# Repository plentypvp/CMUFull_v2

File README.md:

# CMUFull_v2
Цветомузыка на nRF52840. Фото и видео скоро!

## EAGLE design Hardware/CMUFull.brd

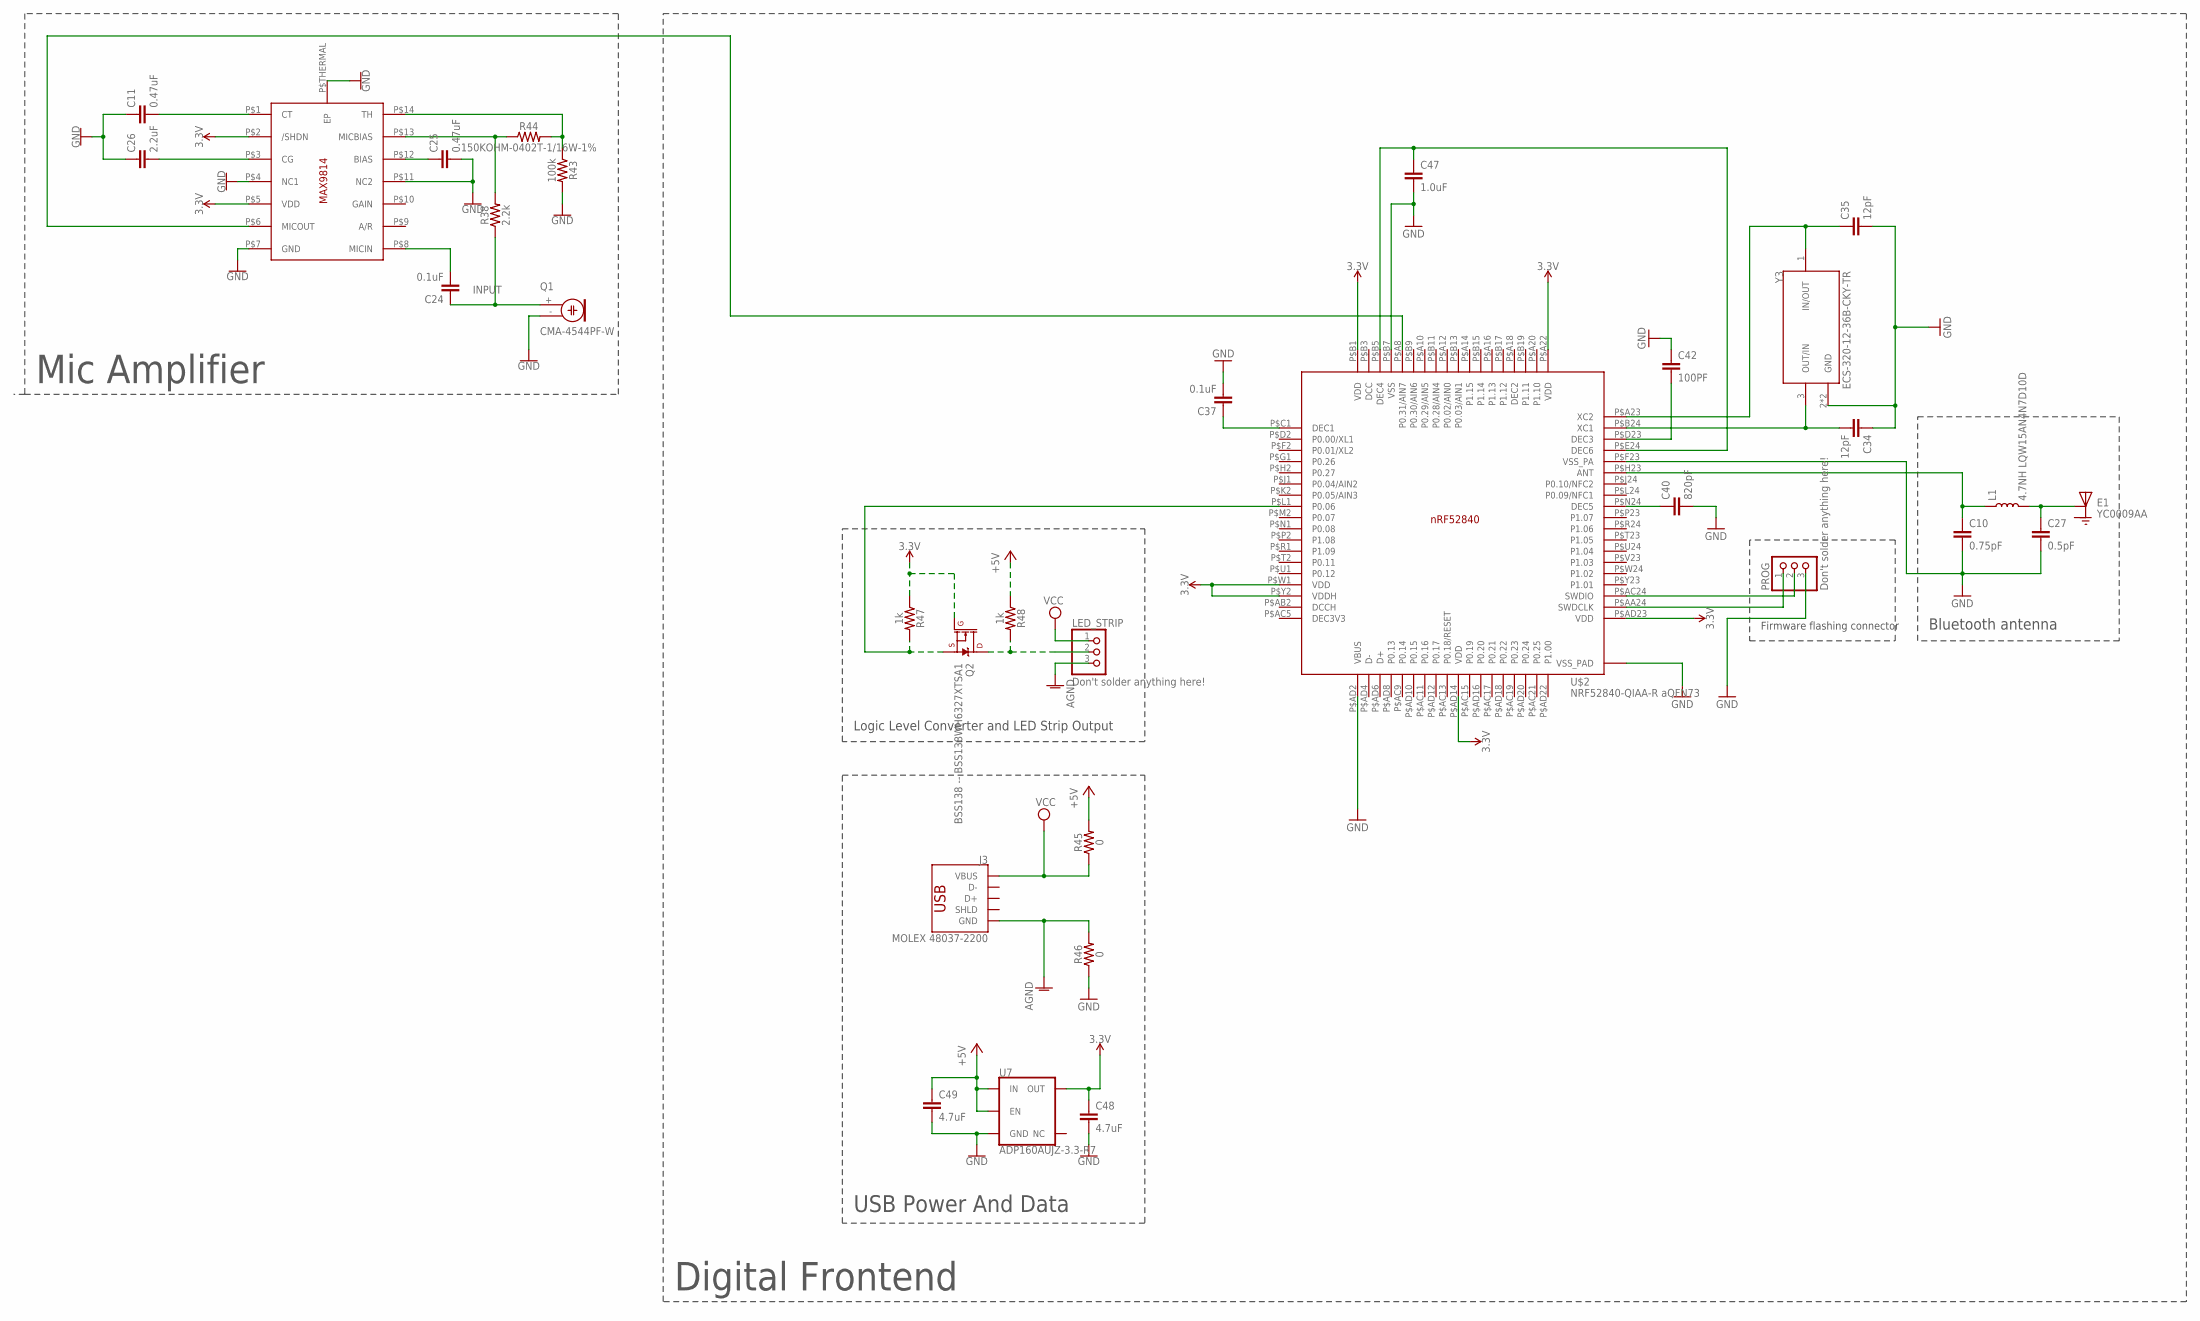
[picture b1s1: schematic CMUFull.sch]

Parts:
C10: 0.75pF; 0402-TIGHT
C11, C25: 0.47uF; 0402-TIGHT
C24, C37: 0.1uF; 0402
C26: 2.2uF; 0402-TIGHT
C27: 0.5pF; 0402-TIGHT
C34, C35: 12pF; 0402-TIGHT
C40: 820pF; 0402
C42: 100PF; 0402
C47: 1.0uF; 0402
C48, C49: 4.7uF; 0402-TIGHT
E1: YC0009AA; XCVR_YC0009AA
J3: MOLEX 48037-2200; USB-A-SMT-MALE
L1: 4.7NH LQW15AN4N7D10D; 0402
LED_STRIP: Don't solder anything here!; 1X03
PROG: Don't solder anything here!; 1X03
Q1: CMA-4544PF-W; 9.7ELECTRET
Q2: BSS138 -- BSS138WH6327XTSA1; SOT23-3
R38: 2.2k; 0402-TIGHT
R43: 100k; 0402-TIGHT
R44: 150KOHM-0402T-1/16W-1%; 0402-TIGHT
R45, R46: 0; 0402
R47, R48: 1k; 0402-TIGHT
U7: ADP160AUJZ-3.3-R7; SOT23-5
U$1: MAX9814ETD+T; TDFN14_3X3MM
U$2: NRF52840-QIAA-R aQFN73; AQFN50P700X700X85_HS-74N
Y3: ECS-320-12-36B-CKY-TR; XTAL_ECS-163.84-10-36-JGN-TR

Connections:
3.3V: C48.1, Q2.1 (G), R47.1, U7.5 (OUT), U$1.P$2 (/SHDN), U$1.P$5 (VDD), U$2.P$A22 (VDD), U$2.P$AD14 (VDD), U$2.P$AD23 (VDD), U$2.P$B1 (VDD), U$2.P$W1 (VDD), U$2.P$Y2 (VDDH)
+5V: C49.1, R45.2, R48.1, U7.1 (IN), U7.3 (EN)
AGND: J3.GND1 (GND), LED_STRIP.3, R46.2
GND: C10.2, C11.1, C25.2, C26.1, C27.2, C34.1, C35.2, C37.2, C40.2, C42.1, C47.2, C48.2, C49.2, E1.2 (GND), E1.3 (GND), PROG.3, Q1.- (1), R43.2, R46.1, U7.2 (GND), U$1.P$4 (NC1), U$1.P$7 (GND), U$1.P$11 (NC2), U$1.P$THERMAL (EP), U$2.P$74 (VSS_PAD), U$2.P$AD2 (VBUS), U$2.P$B7 (VSS), U$2.P$F23 (VSS_PA), Y3.2 (GND), Y3.4 (GND)
INPUT: C24.1, Q1.+ (2), R38.1
unnamed: U$1.P$6 (MICOUT), U$2.P$A8 (P0.31/AIN7)
unnamed: C25.1, U$1.P$12 (BIAS)
unnamed: C24.2, U$1.P$8 (MICIN)
unnamed: C11.2, U$1.P$1 (CT)
unnamed: C26.2, U$1.P$3 (CG)
unnamed: R43.1, R44.2, U$1.P$14 (TH)
unnamed: R38.2, R44.1, U$1.P$13 (MICBIAS)
unnamed: C35.1, U$2.P$A23 (XC2), Y3.1 (IN/OUT)
unnamed: C34.2, U$2.P$B24 (XC1), Y3.3 (OUT/IN)
unnamed: C37.1, U$2.P$C1 (DEC1)
unnamed: PROG.1, U$2.P$AA24 (SWDCLK)
unnamed: PROG.2, U$2.P$AC24 (SWDIO)
unnamed: LED_STRIP.2, Q2.3 (D), R48.2
unnamed: C47.1, U$2.P$B5 (DEC4), U$2.P$E24 (DEC6)
unnamed: C40.1, U$2.P$N24 (DEC5)
unnamed: C42.2, U$2.P$D23 (DEC3)
unnamed: C10.1, L1.1, U$2.P$H23 (ANT)
unnamed: C27.1, E1.1 (INPUT), L1.2
unnamed: Q2.2 (S), R47.2, U$2.P$L1 (P0.06)
VCC: J3.VBUS1 (VBUS), LED_STRIP.1, R45.1

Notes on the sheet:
Mic Amplifier
Logic Level Converter and LED Strip Output
USB Power And Data
Bluetooth antenna
Firmware flashing connector
Digital Frontend

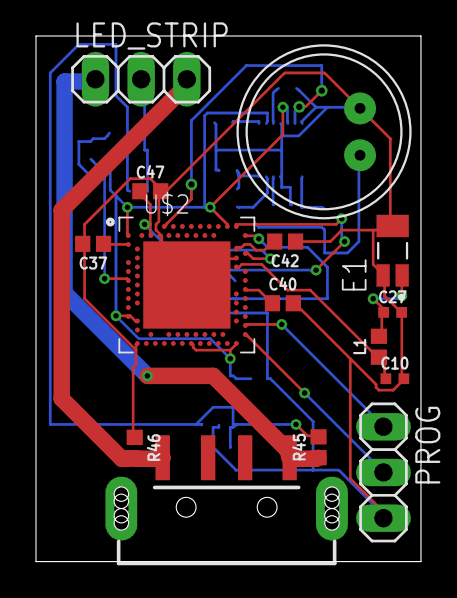
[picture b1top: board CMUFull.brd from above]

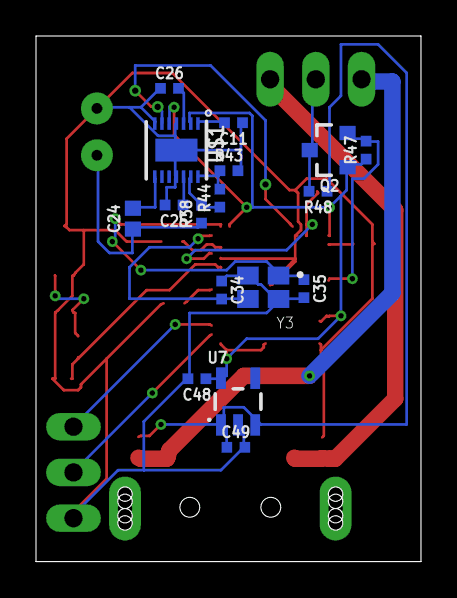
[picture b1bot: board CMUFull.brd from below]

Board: 2 copper layers, 21.4 x 29.2 mm, 32 parts (17 on the bottom side), 25 nets.

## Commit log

2022-01-16 First commit to GitHub, everything triple checked!
2022-01-16 Add README

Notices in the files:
parts and their libraries:
SparkFun-Capacitors: Licensing: Creative Commons ShareAlike 4.0 International - https://creativecommons.org/licenses/by-sa/4.0
